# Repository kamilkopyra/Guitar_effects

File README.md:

Archive repo where I shared my start in the audio-electronics world

# Guitar effects

This repository documents my personal journey into guitar and audio electronics — designing, prototyping, and refining analog and digital effects.

I'm exploring how analog circuitry and digital control can shape guitar tone — from simple transistor fuzzes to complex delay and modulation effects.
Each project reflects a step in learning design, layout, and sound-shaping.

## Projects

Listed in the order I built them.

| # | Project | Photo | What's inside |
|---|---------|-------|---------------|
| 1 | [Fuzz](01-fuzz) |  | schematic (KiCad), audio demo |
| 2 | [Tremolo](02-tremolo) |  | audio demo |
| 3 | [Octafuzz](03-octafuzz) |  | 3D enclosure (Fusion 360) |
| 4 | [Rat distortion](04-rat) |  | 3D enclosure (Fusion 360), audio demo |
| 5 | [PT2399 echo](05-echo) | — | schematic + PCB (KiCad) |

## Tools

- **KiCad** – schematics and PCB layouts
- **Fusion 360** – enclosure design, 3D printed

## Disclaimer

This repository was created for educational purposes only.
Please keep in mind that I'm still learning electronics, PCB and 3D design — so some projects might not be perfect, but they're part of my learning process.

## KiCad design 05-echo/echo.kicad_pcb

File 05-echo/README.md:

# PT2399 echo

This build was my fifth guitar pedal design, and for this project I wanted to take things a step further —
it was the first time I designed a PCB from scratch.

The circuit is based on the **PT2399** chip, a digital delay IC. My design improves on the reference circuit from the PT2399 datasheet:

- two controls: **delay time** and **repetitions**
- input and output buffers for better sound quality
- changes to the sound filtering

## Files

- [`echo.kicad_sch`](echo.kicad_sch) – schematic (KiCad)
- [`echo.kicad_pcb`](echo.kicad_pcb) – PCB layout (KiCad)

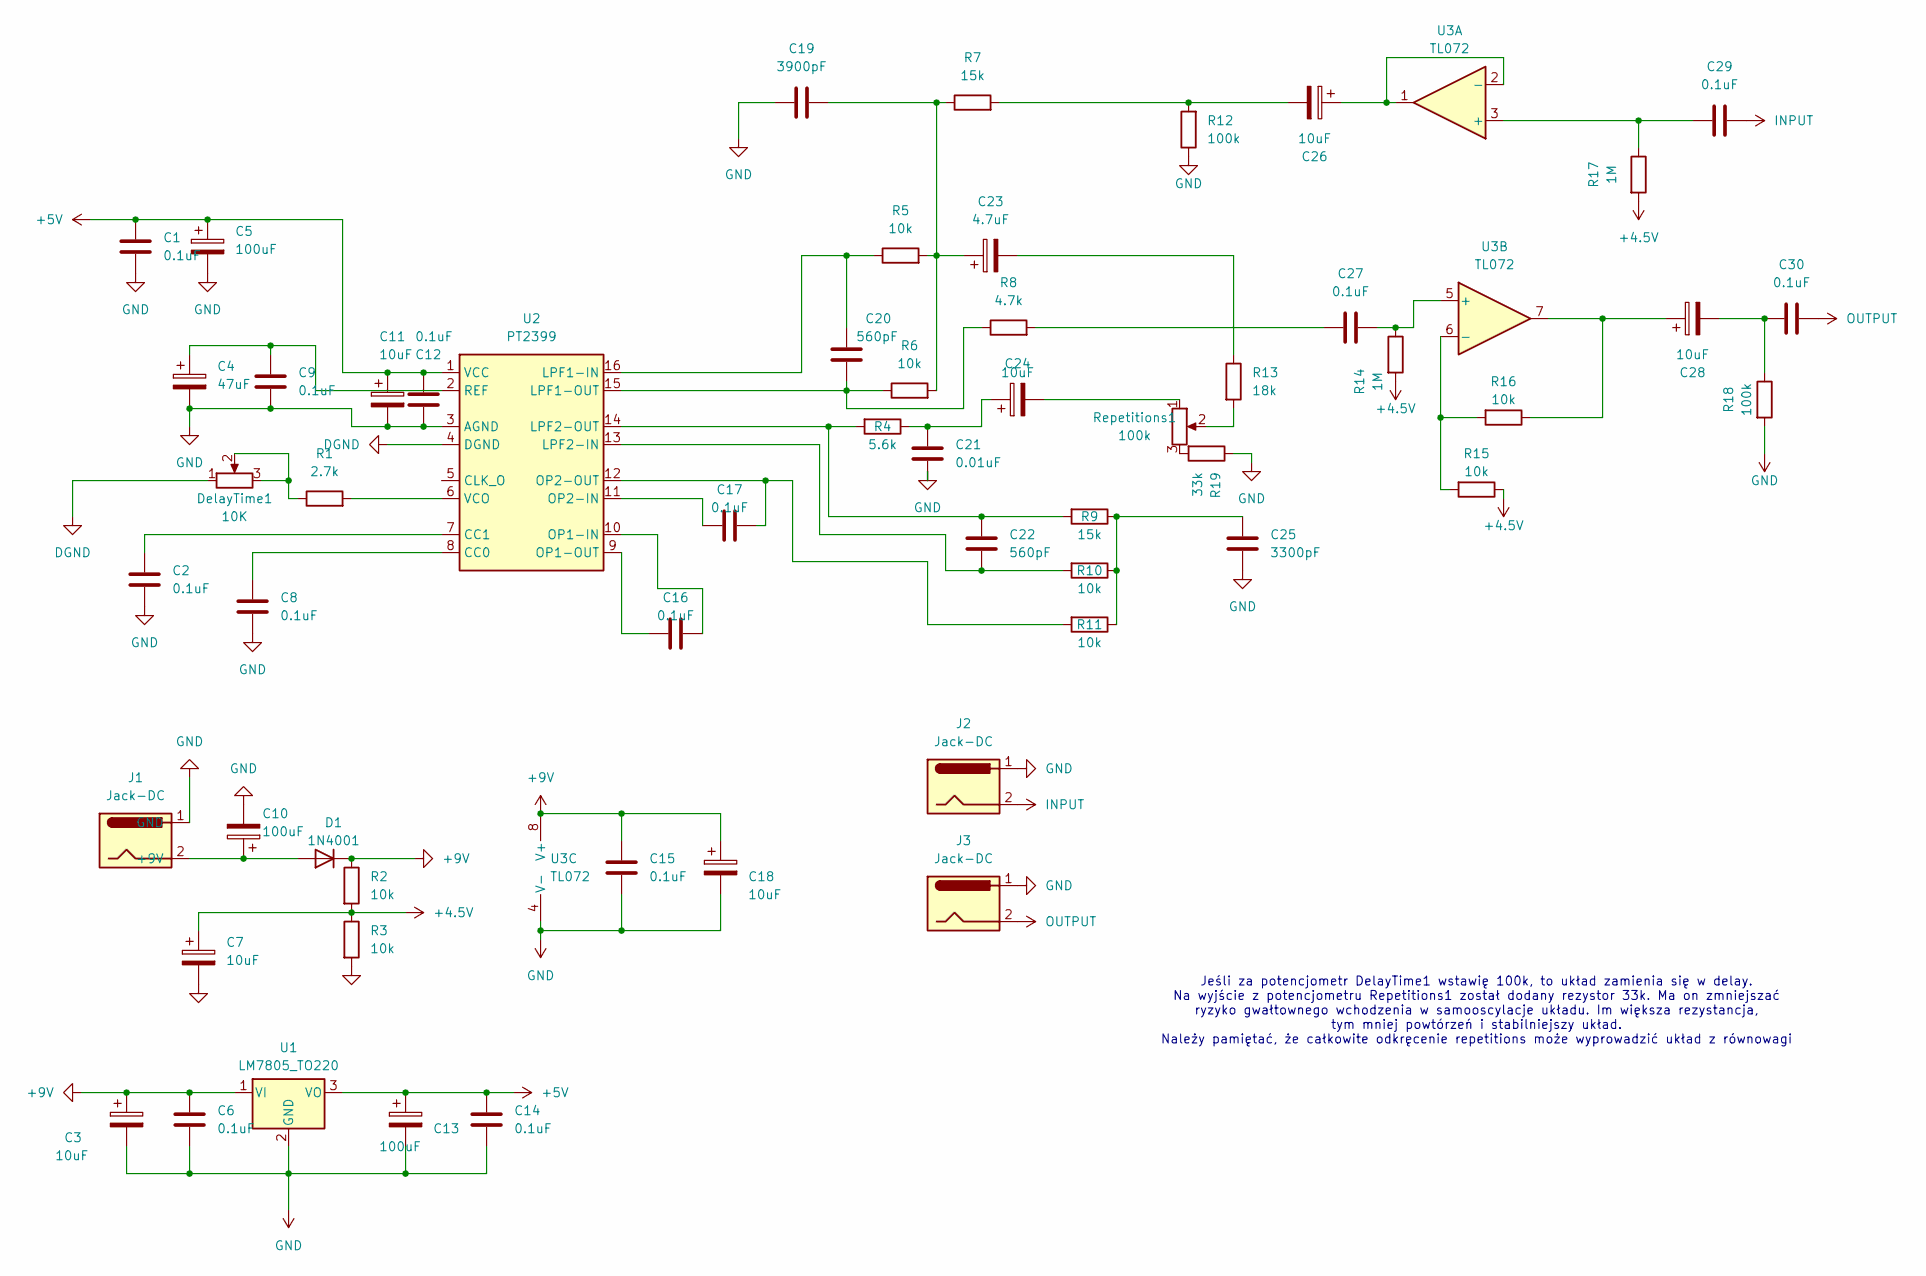
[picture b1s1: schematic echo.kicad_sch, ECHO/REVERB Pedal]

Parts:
C1, C2, C6, C8, C9, C12, C14, C15, C16, C17, C27, C29, C30: 0.1uF; C_Disc_D3.8mm_W2.6mm_P2.50mm
C3, C7, C11, C18, C24, C26, C28: 10uF; CP_Radial_D5.0mm_P2.00mm
C4: 47uF; CP_Radial_D5.0mm_P2.00mm
C5, C10, C13: 100uF; CP_Radial_D5.0mm_P2.00mm
C19: 3900pF; C_Disc_D3.8mm_W2.6mm_P2.50mm
C20, C22: 560pF; C_Disc_D3.8mm_W2.6mm_P2.50mm
C21: 0.01uF; C_Disc_D3.8mm_W2.6mm_P2.50mm
C23: 4.7uF; CP_Radial_D5.0mm_P2.00mm
C25: 3300pF; C_Disc_D3.8mm_W2.6mm_P2.50mm
D1: 1N4001; D_DO-41_SOD81_P10.16mm_Horizontal
DelayTime1: 10K; Potencjometr
J1, J2, J3: Jack-DC; Jack
R1: 2.7k; R_Axial_DIN0207_L6.3mm_D2.5mm_P7.62mm_Horizontal
R2, R3, R5, R6, R10, R11, R15, R16: 10k; R_Axial_DIN0207_L6.3mm_D2.5mm_P7.62mm_Horizontal
R4: 5.6k; R_Axial_DIN0207_L6.3mm_D2.5mm_P7.62mm_Horizontal
R7, R9: 15k; R_Axial_DIN0207_L6.3mm_D2.5mm_P7.62mm_Horizontal
R8: 4.7k; R_Axial_DIN0207_L6.3mm_D2.5mm_P7.62mm_Horizontal
R12, R18: 100k; R_Axial_DIN0207_L6.3mm_D2.5mm_P7.62mm_Horizontal
R13: 18k; R_Axial_DIN0207_L6.3mm_D2.5mm_P7.62mm_Horizontal
R14, R17: 1M; R_Axial_DIN0207_L6.3mm_D2.5mm_P7.62mm_Horizontal
R19: 33k; R_Axial_DIN0207_L6.3mm_D2.5mm_P7.62mm_Horizontal
Repetitions1: 100k; Potencjometr
U1: LM7805_TO220; TO-220-3_Vertical
U2: PT2399; DIP-16_W7.62mm
U3: TL072; DIP-8_W7.62mm_Socket

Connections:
+4.5V: C7.1, R2.2, R3.1, R14.2, R15.1, R17.2
+5V: C1.1, C5.1, C11.1, C12.1, C13.1, C14.1, U1.3 (VO), U2.1 (VCC)
+9V: C3.1, C6.1, C15.1, C18.1, D1.1 (K), R2.1, U1.1 (VI), U3.8 (V+)
DGND: DelayTime1.1, U2.4 (DGND)
GND: C1.2, C2.2, C3.2, C4.2, C5.2, C6.2, C7.2, C8.2, C9.2, C10.2, C11.2, C12.2, C13.2, C14.2, C15.2, C18.2, C19.1, C21.2, C25.2, J1.1 (GND), J2.1, J3.1, R3.2, R12.1, R18.2, R19.1, U1.2 (GND), U2.3 (AGND), U3.4 (V-)
INPUT: C29.2, J2.2
unnamed: C19.2, C23.1, R5.2, R6.2, R7.1
unnamed: C21.1, C24.1, R4.1
unnamed: C23.2, R13.1
unnamed: C24.2, Repetitions1.1
unnamed: C25.1, R9.1, R10.1, R11.1
unnamed: C26.2, R7.2, R12.2
unnamed: C27.1, R8.2
unnamed: C28.1, R16.1, U3.7
unnamed: C28.2, C30.1, R18.1
unnamed: C10.1, D1.2 (A), J1.2 (+9V)
unnamed: DelayTime1.2, DelayTime1.3, R1.1
unnamed: R13.2, Repetitions1.2
unnamed: R19.2, Repetitions1.3
unnamed: C8.1, U2.8 (CC0)
unnamed: C2.1, U2.7 (CC1)
unnamed: C20.1, R5.1, U2.16 (LPF1-IN)
unnamed: C20.2, R6.1, R8.1, U2.15 (LPF1-OUT)
unnamed: C22.2, R10.2, U2.13 (LPF2-IN)
unnamed: C22.1, R4.2, R9.2, U2.14 (LPF2-OUT)
unnamed: C16.2, U2.10 (OP1-IN)
unnamed: C16.1, U2.9 (OP1-OUT)
unnamed: C17.1, U2.11 (OP2-IN)
unnamed: C17.2, R11.2, U2.12 (OP2-OUT)
unnamed: C4.1, C9.1, U2.2 (REF)
unnamed: R1.2, U2.6 (VCO)
unnamed: C29.1, R17.1, U3.3 (+)
unnamed: C26.1, U3.1, U3.2 (-)
unnamed: C27.2, R14.1, U3.5 (+)
unnamed: R15.2, R16.2, U3.6 (-)
OUTPUT: C30.2, J3.2

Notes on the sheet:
Jeśli za potencjometr DelayTime1 wstawię 100k, to układ zamienia się w delay. Na wyjście z potencjometru Repetitions1 został dodany rezystor 33k. Ma on zmniejszać ryzyko gwałtownego wchodzenia w samooscylacje układu. Im większa rezystancja, tym mniej powtórzeń i stabilniejszy układ. Należy pamiętać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

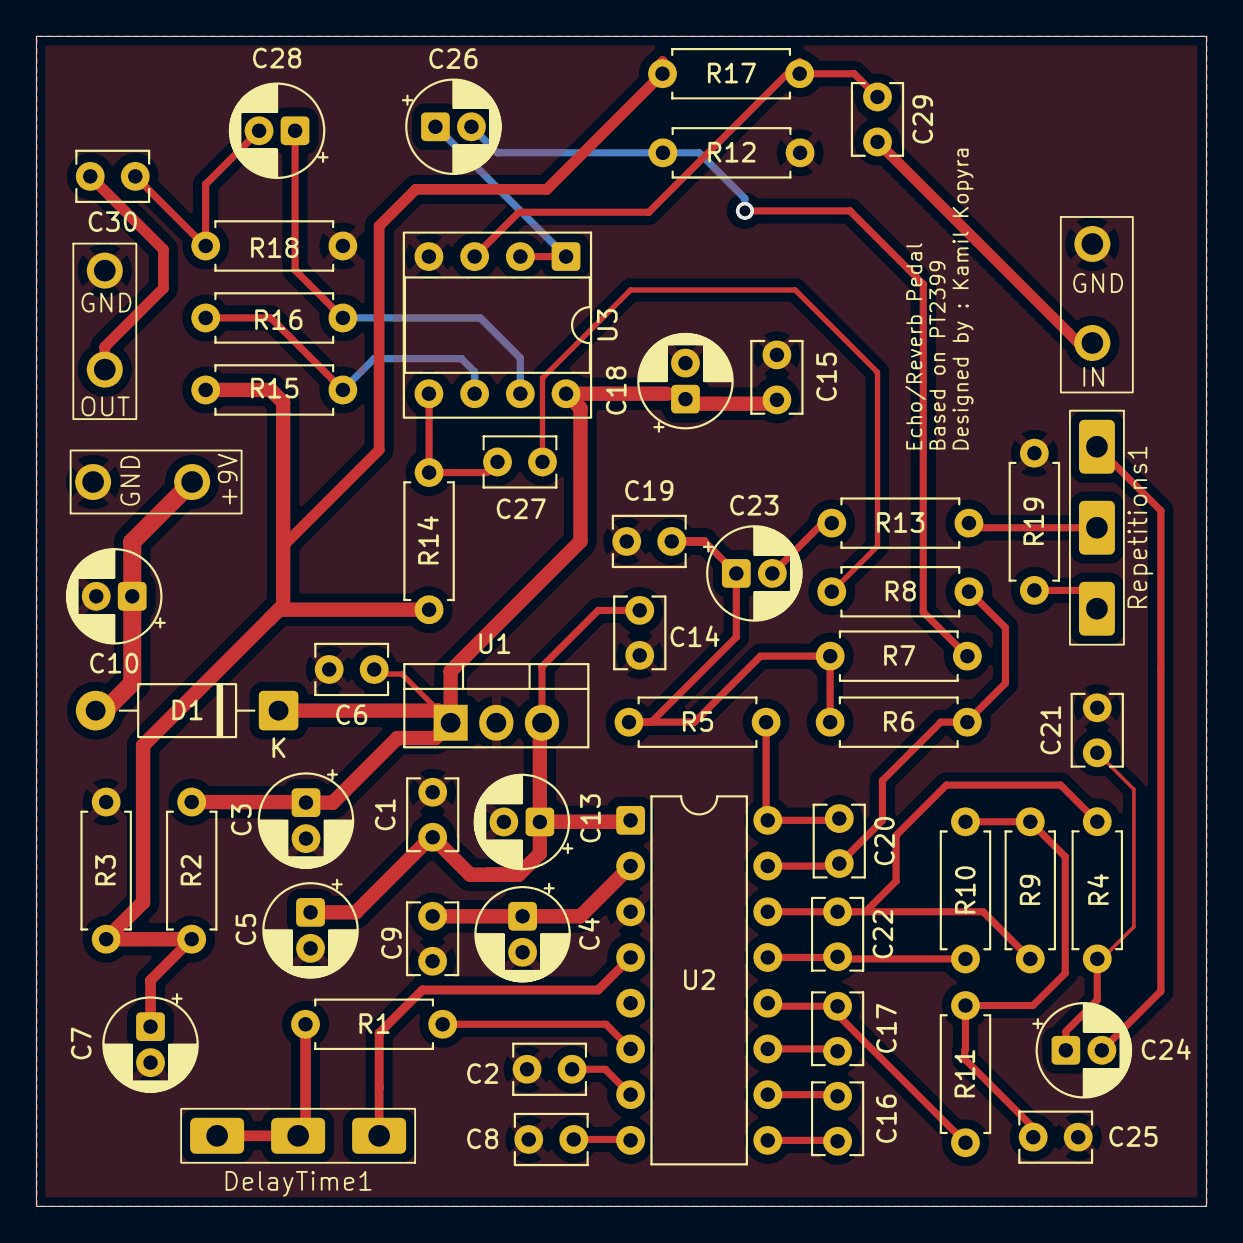
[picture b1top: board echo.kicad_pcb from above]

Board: 2 copper layers, 65.0 x 65.0 mm, 56 parts (0 on the bottom side), 36 nets.

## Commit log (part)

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2025-10-14 Rename booster.README.md to fuzz
2025-10-14 Create schematic
2025-10-14 Rename IMG_0680.mp4 to audio_demo
2025-10-14 Rename IMG_0676.jpeg to Finished_build
2025-10-14 Create asa
2025-10-14 Rename tremolo.f3d to tremolo_enclosure_Fusion.f3d
2025-10-14 Rename IMG_0733.mp4 to audio_demo
2025-10-14 Rename IMG_1112.jpeg to Build
2025-10-14 Update and rename Build to build
2025-10-14 Rename IMG_1112.jpeg to finished_build.jpeg
2025-10-14 Create asd
2025-10-14 mv Octafuff octafuzz
2025-10-14 Rename Octafuzz/sdf to octafuzz
2025-10-14 Rename Octafuzz to octafuzz
